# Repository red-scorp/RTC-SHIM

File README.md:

# RTC-SHIM project

RTC-SHIM (mini-HAT), a DS3231 battery driven real-time clock for Raspberry Pi.

"How did it come to this?" you may ask.
The answer is simple.
I was pissed off by the fact the several Pis I have all have the same issue.
They lose time information when they switched off and need Internet to set proper time again.
The obvious reason for this is lack of RTC chip and backup battery to count time when main CPU of Pi is off.
This is how it's done in all modern PCs and notebooks (and Macs too).
I've searched Internet and found no solution which suits my needs.

- The RTC board should be mounted on 40-pin connector of Raspberry Pi (like 2, 3, 4, zero have).
- The board should be mechanically and electrically compatible with all modern Pis (3+, 4, zero WH).
- The board should be mounted inside or outside the Pi's case.
- There should be possible to put some Pi HAT (Hardware Attached on Top) on top of the board (like LCD display, LoRa, LEDs array or 3G/4G modem HATs).
- The board should be obviously small enough to fit in case of Pi.
- The board should have a battery holder or/and a common notebook BIOS battery connector.
- The board should be easy to setup under Pi's Linux (like Raspbian or Ubuntu).
- The board should be cheap to buy or/and easy to manufacture by (my) hand at home.

And gradually I came with few designs presented here.

## RTC-SHIM

Raspberry Pi 40-pin **RTC-SHIM** mini-HAT.

Preview:

[Schematics in PDF format](doc/RTC-SHIM.pdf)

Features:

- DS3231 RTC chip
- double footprint for larger and smaller versions of the chip
- CR1220 3V battery
- locked Pi headers
- double set of Pi headers (for inside and outside mount)
- I2C0/I2C1 bus selection
- can be used as SHIM (no headers) or HAT (with headers)
- optional external notebook BIOS battery connector

CAM files are available.

## RTC-mini-flip-SHIM

Raspberry Pi **RTC-mini-flip-SHIM** micro-HAT.

Preview:

[Schematics in PDF format](doc/RTC-mini-flip-SHIM.pdf)

Features:

- DS3231 RTC chip
- double footprint for larger and smaller versions of the chip
- CR1220 3V battery
- locked Pi headers
- double mount on Pi headers (for inside and outside mount)
- very small size
- fits on 26- and 40-pin Pi headers
- optional external notebook BIOS battery connector (both side mount possible)

CAM files are available.

## RTC-zero-SHIM

Raspberry Pi zero 40-pin **RTC-zero-SHIM** mini-HAT.

Preview:

[Schematics in PDF format](doc/RTC-zero-SHIM.pdf)

Features:

- DS3231 RTC chip
- double footprint for larger and smaller versions of the chip
- CR2032/CR1220 3V battery
- locked Pi headers
- Pi zero board style
- I2C0/I2C1 bus selection
- can be used as SHIM (no headers) or HAT (with headers)
- optional external notebook BIOS battery connector

CAM files are available.

## BOM

Bill Of Materials is currently available only for LCSC Electronic Components Distributor, which is probably cheapest anyway.

### LCSC BOM

|Designator  |Part/Value  |Package/Footprint     |LCSC # |
|------------|------------|----------------------|-------|
|BAT1        |CR1220-2    |SMD                   |C70381 |
|BAT2        |BS-8-1      |SMD                   |C70378 |
|C1\*\*      |Cap. 100nF  |0402                  |C1525  |
|C2\*\*      |Cap. 1uF    |0603                  |C15849 |
|IC1\*       |DS3231SN#T&R|SOIC-16_300mil        |C9866  |
|IC2\*       |DS3231MZ+TRL|SOIC-8_150mil         |C107410|
|LIPO1, LIPO2|A1251WV-2P  |Through Hole,P=1.25mm |C225090|
|R1, R2\*\*  |Res. 10K    |0402                  |C25744 |

\*) Only one of chips should be installed, either IC1 or IC2.
\*\*) These passive components are optional but it's recommended to install them.

## Links

- [pinout.xyz](https://pinout.xyz/) - a brilliant resource on topic of Pi's pinout and HATs.
- [raspberrypi/hats](https://github.com/raspberrypi/hats) - Pi's HAT specification.
- [RPI_RTC_Module_SKU:EP-0016](https://wiki.52pi.com/index.php/RPI_RTC_Module_SKU:EP-0016) - some RTC schematics and setup info.
- [Raspberry Pi RTC: Adding a Real Time Clock](https://pimylifeup.com/raspberry-pi-rtc/) - RTC setup info.

## How to help

Your contributions as code, resources, or finances are welcome! Please contact me directly via email at andriy.golovnya@gmail.com or through my [GitHub profile](https://github.com/red-scorp).

If you'd like to make a financial contribution, you can donate via [PayPal](http://paypal.me/redscorp) or [Ko-Fi](http://ko-fi.com/redscorp). Your support is greatly appreciated.

Thanks in advance!

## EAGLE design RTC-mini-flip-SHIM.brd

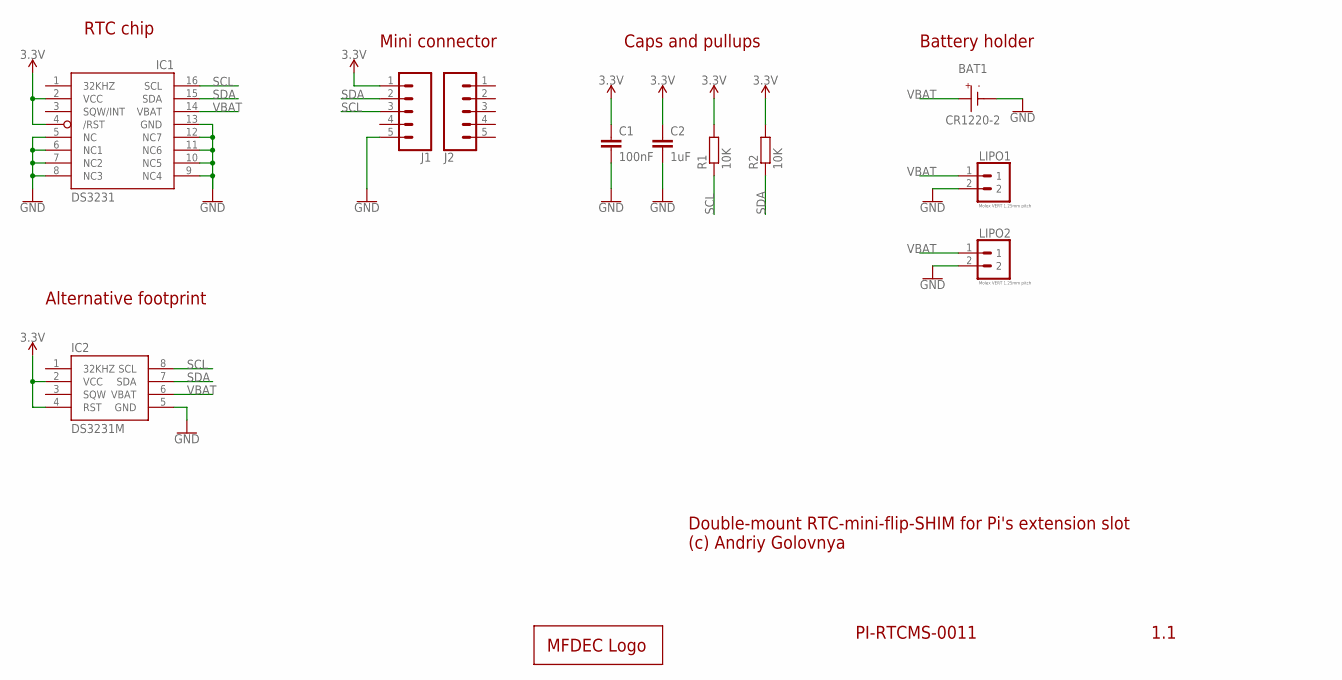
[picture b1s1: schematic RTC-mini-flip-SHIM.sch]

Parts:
BAT1: CR1220-2
C1: 100nF; C0402
C2: 1uF; C0603
IC1: DS3231/SO; SO16W
IC2: DS3231M; SO08
J1, J2: CONN_05LOCK; 1X05_LOCK
LIPO1, LIPO2: Molex VERT 1.25mm pitch; _MOLEX-0530470210_VERT_PITCH-1.25MM
LOGO1: MFDECLOGO_L_10MM; MFDEC_L_10MM
R1, R2: 10K; R0402

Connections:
3.3V: C1.1, C2.1, IC1.2 (VCC), IC1.4 (/RST), IC2.2 (VCC), IC2.4 (RST), J1.1, R1.2, R2.2
GND: BAT1.BAT-, C1.2, C2.2, IC1.5 (NC), IC1.6 (NC1), IC1.7 (NC2), IC1.8 (NC3), IC1.9 (NC4), IC1.10 (NC5), IC1.11 (NC6), IC1.12 (NC7), IC1.13 (GND), IC2.5 (GND), J1.5, LIPO1.2, LIPO2.2
SCL: IC1.16 (SCL), IC2.8 (SCL), J1.3, R1.1
SDA: IC1.15 (SDA), IC2.7 (SDA), J1.2, R2.1
VBAT: BAT1.BAT+, IC1.14 (VBAT), IC2.6 (VBAT), LIPO1.1, LIPO2.1

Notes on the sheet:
1.1
PI-RTCMS-0011
Double-mount RTC-mini-flip-SHIM for Pi's extension slot (c) Andriy Golovnya
RTC chip
Caps and pullups
Mini connector
Battery holder
Alternative footprint

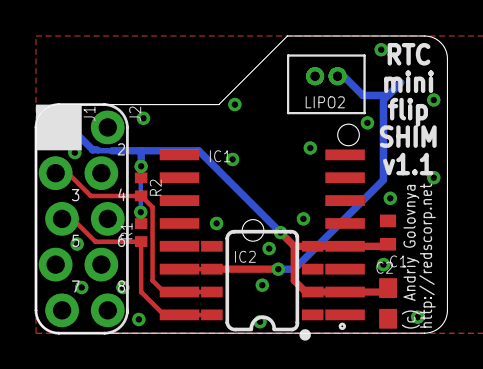
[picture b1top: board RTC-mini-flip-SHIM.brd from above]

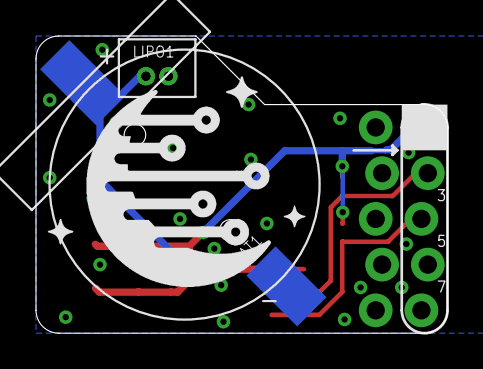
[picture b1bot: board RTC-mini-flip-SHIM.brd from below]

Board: 2 copper layers, 22.9 x 16.5 mm, 12 parts (3 on the bottom side), 5 nets.

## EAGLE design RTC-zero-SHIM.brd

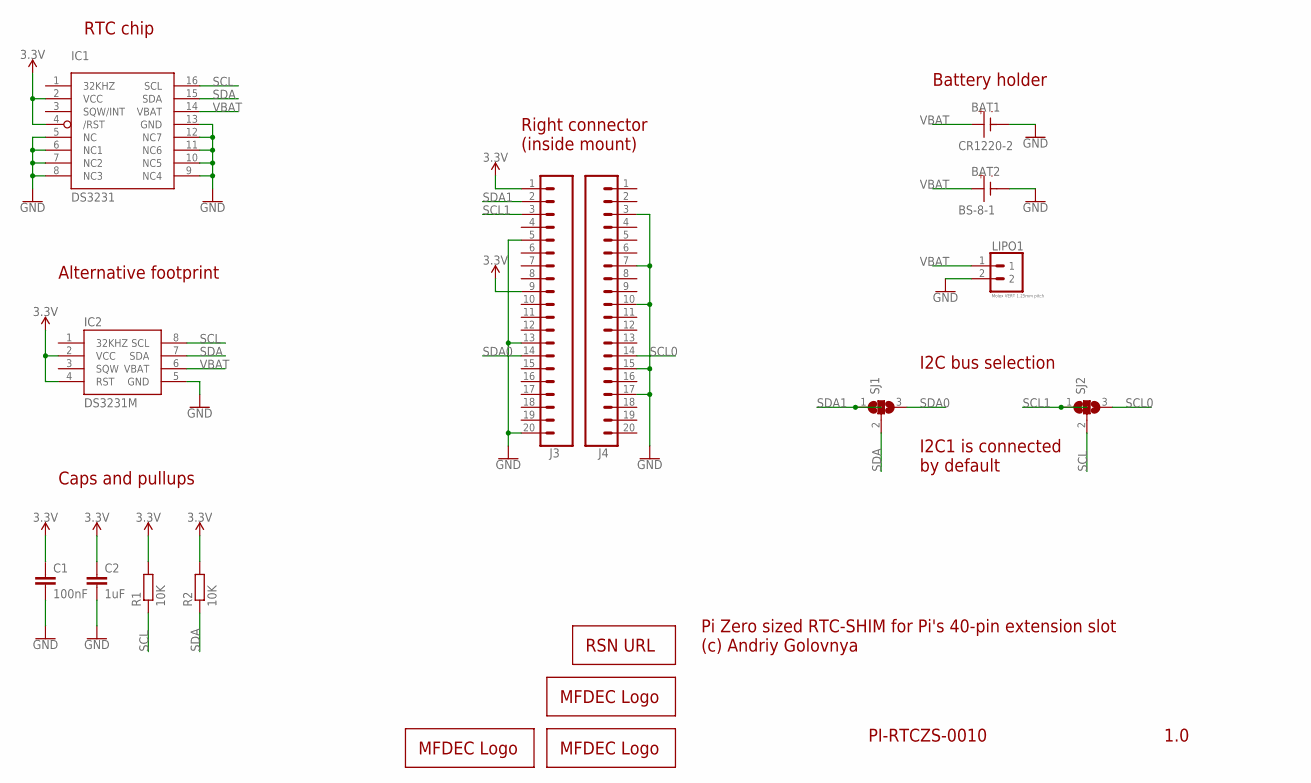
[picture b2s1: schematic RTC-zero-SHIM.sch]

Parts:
BAT1: CR1220-2
BAT2: BS-8-1
C1: 100nF; C0402
C2: 1uF; C0603
IC1: DS3231/SO; SO16W
IC2: DS3231M; SO08
J3, J4: CONN_20LOCK; 1X20_LOCK
LIPO1: Molex VERT 1.25mm pitch; _MOLEX-0530470210_VERT_PITCH-1.25MM
LOGO1: MFDECLOGO_SQ_8MM; MFDEC_SQ_8MM
LOGO2: MFDECLOGO_L_30MM; MFDEC_L_30MM
LOGO3: RSNURL_QR_10MM
LOGO4: MFDECLOGO_L_10MM; MFDEC_L_10MM
R1, R2: 10K; R0402
SJ1, SJ2: SJ2; SJ_2

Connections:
3.3V: C1.1, C2.1, IC1.2 (VCC), IC1.4 (/RST), IC2.2 (VCC), IC2.4 (RST), J3.1, J3.9, R1.2, R2.2
GND: BAT1.BAT-, BAT2.BAT-, C1.2, C2.2, IC1.5 (NC), IC1.6 (NC1), IC1.7 (NC2), IC1.8 (NC3), IC1.9 (NC4), IC1.10 (NC5), IC1.11 (NC6), IC1.12 (NC7), IC1.13 (GND), IC2.5 (GND), J3.5, J3.13, J3.20, J4.3, J4.7, J4.10, J4.15, J4.17, LIPO1.2
SCL: IC1.16 (SCL), IC2.8 (SCL), R1.1, SJ2.2
SCL0: J4.14, SJ2.3
SCL1: J3.3, SJ2.1
SDA: IC1.15 (SDA), IC2.7 (SDA), R2.1, SJ1.2
SDA0: J3.14, SJ1.3
SDA1: J3.2, SJ1.1
VBAT: BAT1.BAT+, BAT2.BAT+, IC1.14 (VBAT), IC2.6 (VBAT), LIPO1.1

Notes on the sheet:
1.0
PI-RTCZS-0010
Pi Zero sized RTC-SHIM for Pi's 40-pin extension slot (c) Andriy Golovnya
RTC chip
Caps and pullups
Right connector (inside mount)
I2C bus selection
I2C1 is connected by default
Battery holder
Alternative footprint

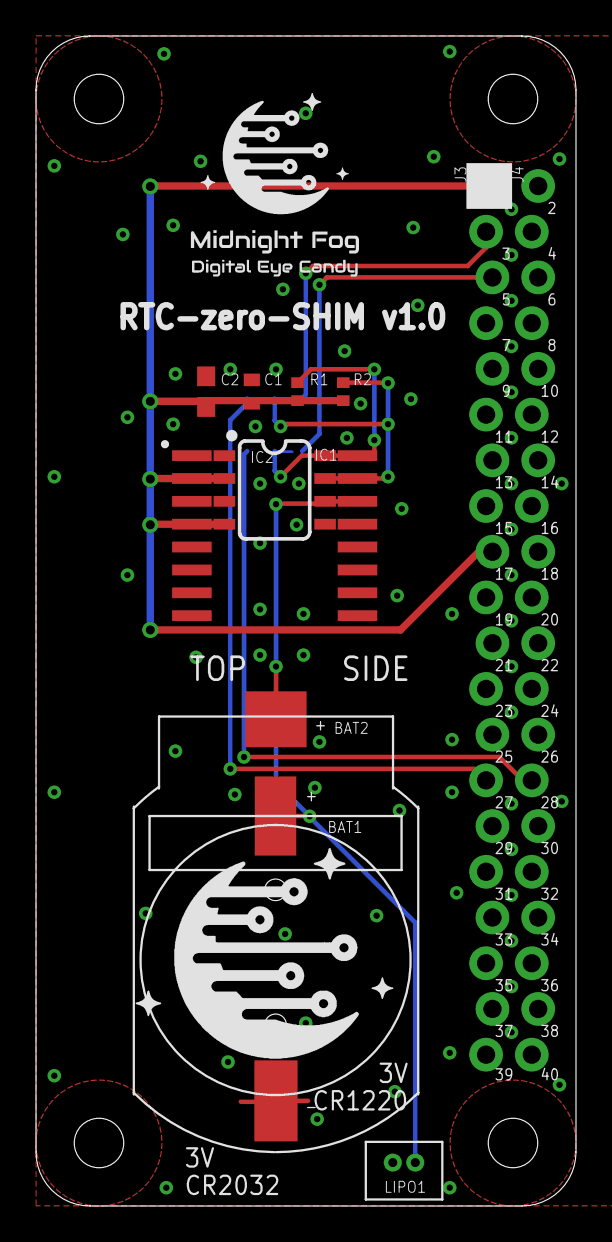
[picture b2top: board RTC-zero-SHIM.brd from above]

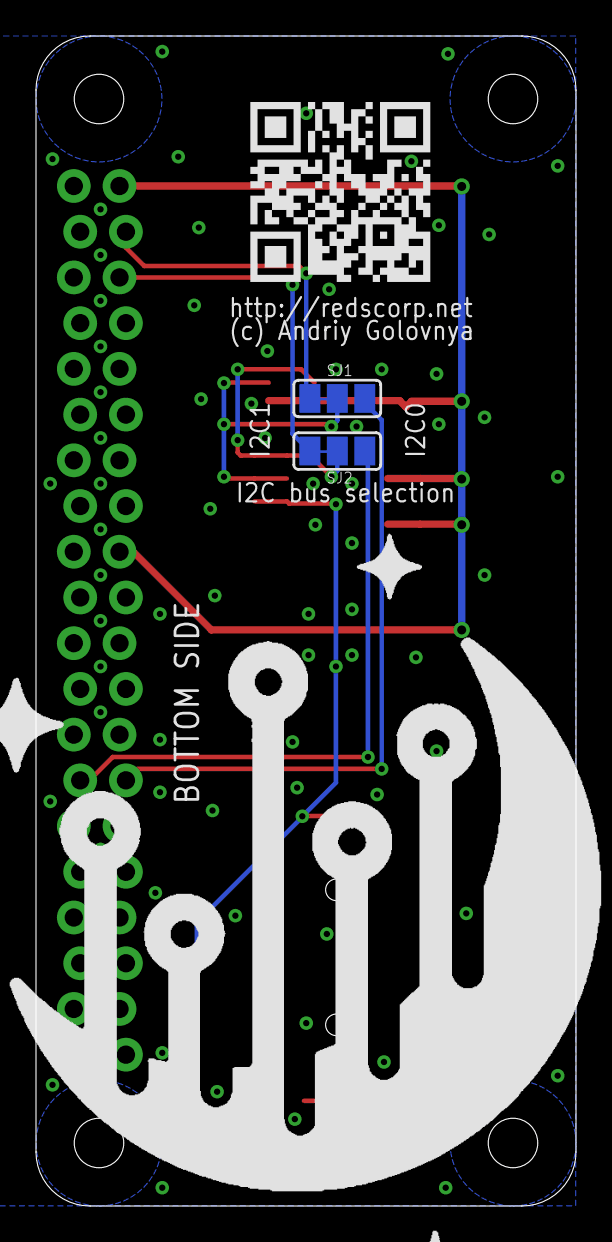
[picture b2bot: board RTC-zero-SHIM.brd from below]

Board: 2 copper layers, 30.0 x 65.0 mm, 17 parts (4 on the bottom side), 9 nets.

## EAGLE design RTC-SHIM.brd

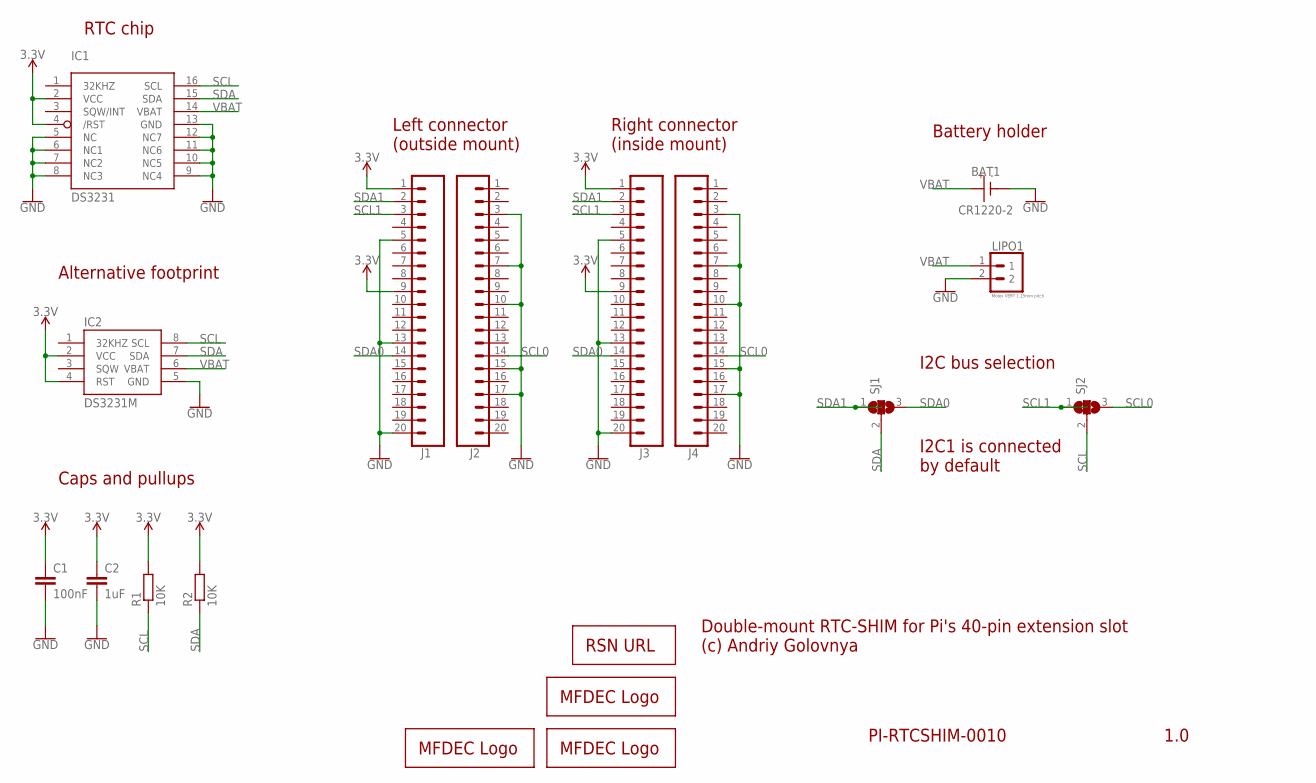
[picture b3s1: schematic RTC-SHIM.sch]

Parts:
BAT1: CR1220-2
C1: 100nF; C0402
C2: 1uF; C0603
IC1: DS3231/SO; SO16W
IC2: DS3231M; SO08
J1, J2, J3, J4: CONN_20LOCK; 1X20_LOCK
LIPO1: Molex VERT 1.25mm pitch; _MOLEX-0530470210_VERT_PITCH-1.25MM
LOGO1: MFDECLOGO_SQ_8MM; MFDEC_SQ_8MM
LOGO2: MFDECLOGO_L_20MM; MFDEC_L_20MM
LOGO3: RSNURL_QR_10MM
LOGO4: MFDECLOGO_L_10MM; MFDEC_L_10MM
R1, R2: 10K; R0402
SJ1, SJ2: SJ2; SJ_2

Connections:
3.3V: C1.1, C2.1, IC1.2 (VCC), IC1.4 (/RST), IC2.2 (VCC), IC2.4 (RST), J1.1, J1.9, J3.1, J3.9, R1.2, R2.2
GND: BAT1.BAT-, C1.2, C2.2, IC1.5 (NC), IC1.6 (NC1), IC1.7 (NC2), IC1.8 (NC3), IC1.9 (NC4), IC1.10 (NC5), IC1.11 (NC6), IC1.12 (NC7), IC1.13 (GND), IC2.5 (GND), J1.5, J1.13, J1.20, J2.3, J2.7, J2.10, J2.15, J2.17, J3.5, J3.13, J3.20, J4.3, J4.7, J4.10, J4.15, J4.17, LIPO1.2
SCL: IC1.16 (SCL), IC2.8 (SCL), R1.1, SJ2.2
SCL0: J2.14, J4.14, SJ2.3
SCL1: J1.3, J3.3, SJ2.1
SDA: IC1.15 (SDA), IC2.7 (SDA), R2.1, SJ1.2
SDA0: J1.14, J3.14, SJ1.3
SDA1: J1.2, J3.2, SJ1.1
VBAT: BAT1.BAT+, IC1.14 (VBAT), IC2.6 (VBAT), LIPO1.1

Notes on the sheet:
1.0
PI-RTCSHIM-0010
Double-mount RTC-SHIM for Pi's 40-pin extension slot (c) Andriy Golovnya
RTC chip
Caps and pullups
Left connector (outside mount)
Right connector (inside mount)
I2C bus selection
I2C1 is connected by default
Battery holder
Alternative footprint

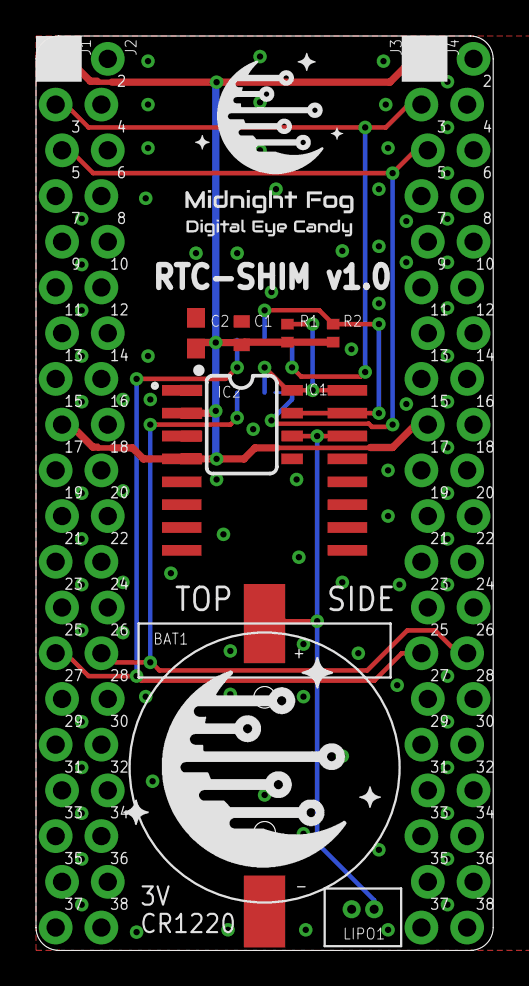
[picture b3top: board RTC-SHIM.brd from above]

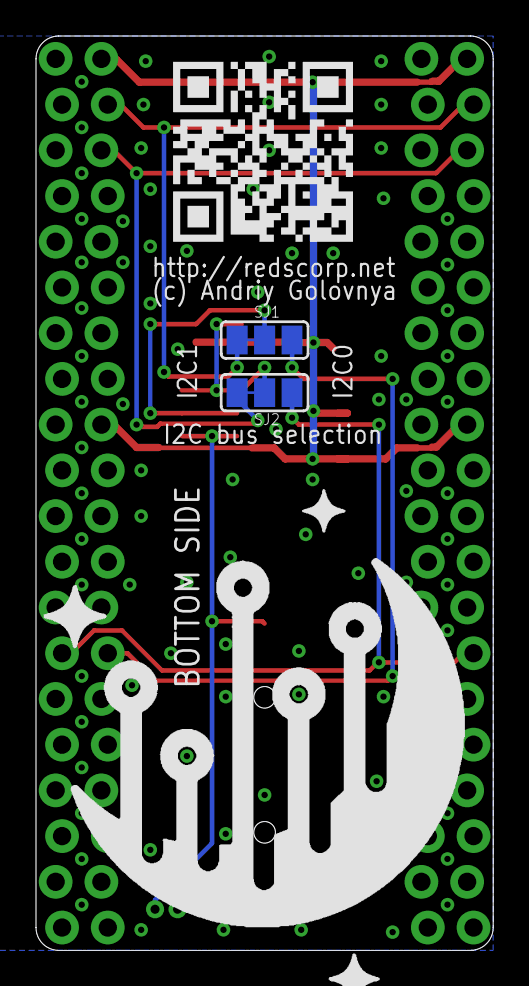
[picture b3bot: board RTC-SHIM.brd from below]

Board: 2 copper layers, 25.4 x 50.8 mm, 18 parts (4 on the bottom side), 9 nets.

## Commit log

2020-11-18 Add basic components for universal RTC SHIM for Pi
2020-11-19 Add 40 pin connectors and solder joins fro I2C bus selection. Add basic board layout.
2020-11-19 Add project description.
2020-11-20 Added Battery holder and some logos and texts.
2020-11-20 Moved stuff around a little bit.
2020-11-21 Trace the board. Add CAM files.
2020-11-21 Added BOM and PnP
2020-11-21 Updated the description
2020-11-22 Add few texts. Move some traces around. Updated description.
2020-11-24 Add RTC-mini-flip-SHIM.
2020-11-25 Removed unneeded traces. generated new CAM.
2020-11-25 Added battery connector. Generated CAM.
2020-11-26 Add CAM for mini SHIM.
2020-11-26 Add battery connector to the front of mini SHIM too. Generate new CAM.
2020-11-26 Updated description
2020-11-26 Updated readmes with CMOS battery connector
2020-11-27 Add schematics in PDF format
2020-11-27 Add board preview images.
2020-11-27 Made preview images smaller.
2020-11-30 Update README.md
    Add LCSC BOM
2020-11-30 Update README.md
    Fix typo
2020-12-02 Add pin numbers on silk.
2020-12-02 Generated new CAM.
2020-12-11 Fixed typo in README.md.
2020-12-11 Fixed few typos.
2020-12-11 Moved some stuff around. Add second footprint. Moved battery away from center for better flipability.
2020-12-11 Generated new PDFs.
2020-12-13 Changed mini SHIM layout. Traced mini SHIM.
2020-12-13 Use more locking pin headers. Moved some traces.
2020-12-14 Updated README.
2020-12-18 Generated new PNG board previews.
2020-12-19 Minor changes in README.
2020-12-21 Added RTC-zero-SHIM design.
2020-12-21 Added new PDF schematics.
2020-12-21 Added new PNG preview image.
2020-12-21 Updated descriptions.
2020-12-21 Fixed descriptions for battery type.
2020-12-31 Adjusted some traces differently. Generated preview PNG. Generated new CAM.
2021-01-04 Fixed typo in README.
2021-01-05 Simplified document names. Generated PDF schematics.
2021-01-08 Moved battery holder and lipo connector a bit down to improve compatibility with other boards.
2021-01-10 Added link to raspberrypi/hats
2021-01-13 Fixed description
2021-01-15 Added second batter holder as alternative. Generated CAM. Generated PDF schematics. Generated PNG preview image.
2021-03-01 Fix readme.
2021-07-29 Make round cutouts in screwing area. Generated CAM files. Generated PNG previews.
2021-08-15 Moved battery socket to another side to not collide with CPU heat sink. Generated CAM files.
2021-08-15 Generated PDF schematics.
2021-12-05 cleanup.
2022-01-24 Added Ko-Fi link
2022-02-06 Updated descriptions
2023-08-28 Updated 'How to help' section.

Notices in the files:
parts and their libraries:
SparkFun-Clocks: Licensing: Creative Commons ShareAlike 4.0 International - https://creativecommons.org/licenses/by-sa/4.0
